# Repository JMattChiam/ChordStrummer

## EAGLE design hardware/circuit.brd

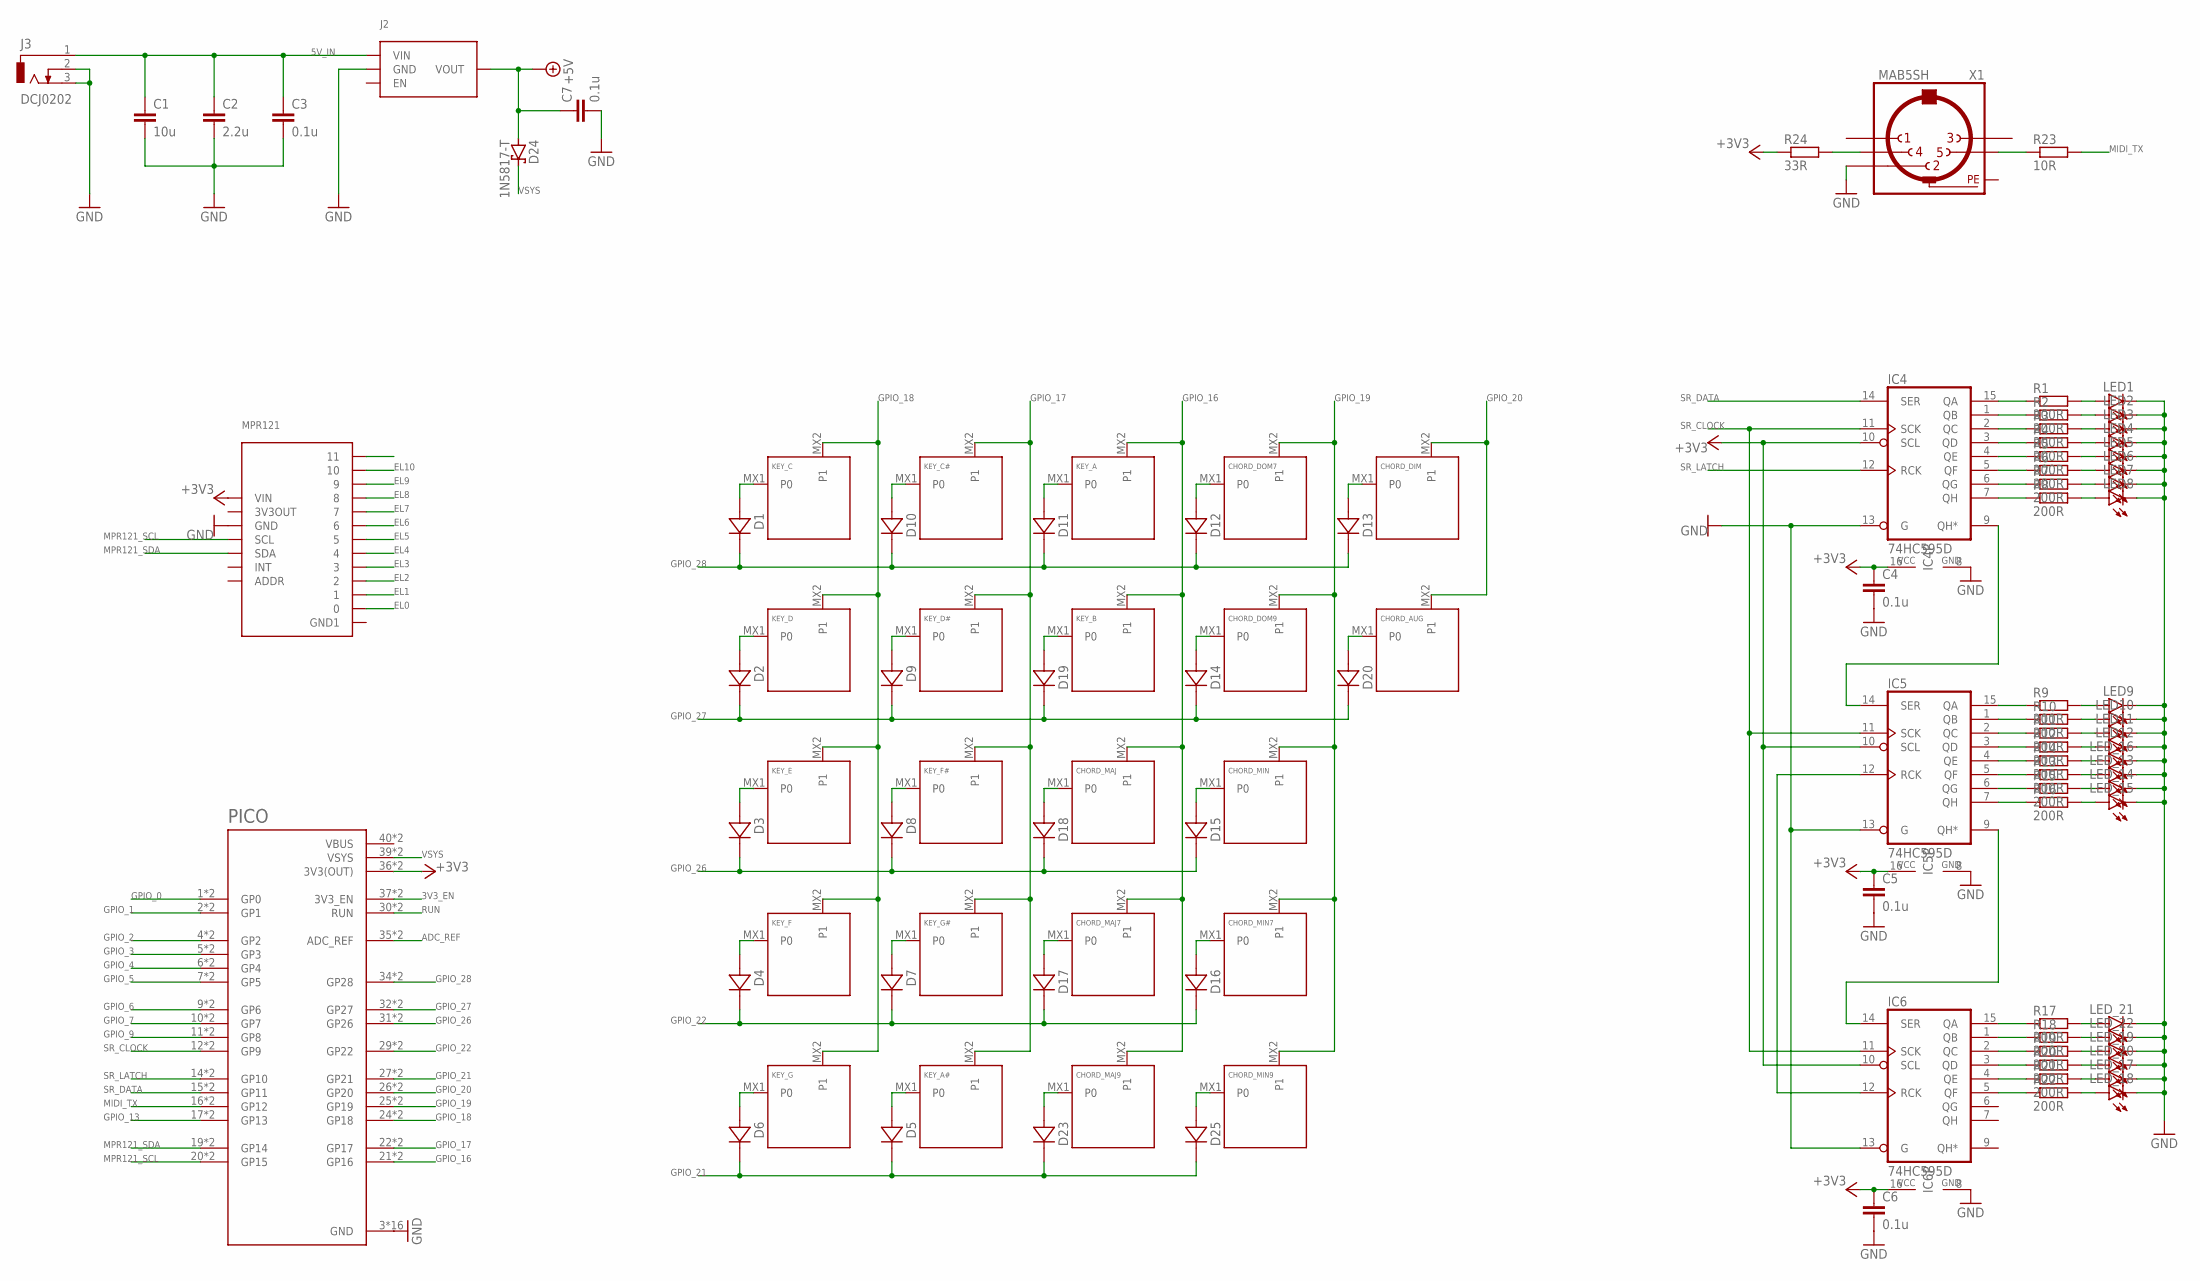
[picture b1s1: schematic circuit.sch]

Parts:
C1: 10u; C5B2.5
C2: 2.2u; C5B2.5
C3, C4, C5, C6, C7: 0.1u; C0805
CHORD_AUG: KEYSWITCH-PLAIN-MX-1U; MX-1U
CHORD_DIM: KEYSWITCH-PLAIN-MX-1U; MX-1U
CHORD_DOM7, CHORD_DOM9: KEYSWITCH-PLAIN-MX-1U; MX-1U
CHORD_MAJ, CHORD_MAJ7, CHORD_MAJ9: KEYSWITCH-PLAIN-MX-1U; MX-1U
CHORD_MIN, CHORD_MIN7, CHORD_MIN9: KEYSWITCH-PLAIN-MX-1U; MX-1U
D1, D2, D3, D4, D5, D6, D7, D8, D9, D10, D11, D12, D13, D14, D15, D16, D17, D18, D19, D20, D23, D25: DIODE-SOD-323; SOD-323
D24: 1N5817-T; DO41-7.6
IC4, IC5, IC6: 74HC595D; SO16
J2: DCDC_MINI_CONVERTER
J3: DCJ0202
KEY_A: KEYSWITCH-PLAIN-MX-1U; MX-1U
KEY_A#: KEYSWITCH-PLAIN-MX-1U; MX-1U
KEY_B: KEYSWITCH-PLAIN-MX-1U; MX-1U
KEY_C: KEYSWITCH-PLAIN-MX-1U; MX-1U
KEY_C#: KEYSWITCH-PLAIN-MX-1U; MX-1U
KEY_D: KEYSWITCH-PLAIN-MX-1U; MX-1U
KEY_D#: KEYSWITCH-PLAIN-MX-1U; MX-1U
KEY_E: KEYSWITCH-PLAIN-MX-1U; MX-1U
KEY_F: KEYSWITCH-PLAIN-MX-1U; MX-1U
KEY_F#: KEYSWITCH-PLAIN-MX-1U; MX-1U
KEY_G: KEYSWITCH-PLAIN-MX-1U; MX-1U
KEY_G#: KEYSWITCH-PLAIN-MX-1U; MX-1U
LED1, LED2, LED3, LED4, LED5, LED6, LED7, LED8, LED9, LED10, LED11, LED12: LEDCHIPLED_0805; CHIPLED_0805
LED_13, LED_14, LED_15, LED_16, LED_17, LED_18, LED_19, LED_20, LED_21, LED_22: LEDCHIPLED_0805; CHIPLED_0805
MPR121: MPR121_ADAFRUIT; ADAFRUIT_MPR121
PICO: RASPBERRY_PICO-NO_DEBUG; PICO-PKG-NO_DEBUG
R1, R2, R3, R4, R5, R6, R7, R8, R9, R10, R11, R12, R13, R14, R15, R16, R17, R18, R19, R20, R21, R22: 200R; R0805
R23: 10R; R0805
R24: 33R; R0805
X1: MAB5SH

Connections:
3V3_EN: PICO.37 (3V3_EN), PICO.P$37 (3V3_EN)
5V_IN: C1.1, C2.1, C3.1, J2.VIN, J3.1
+3V3: C4.1, C5.1, C6.1, IC4.10 (SCL), IC4.16 (VCC), IC5.10 (SCL), IC5.16 (VCC), IC6.10 (SCL), IC6.16 (VCC), MPR121.VCC (VIN), PICO.36 (3V3(OUT)), PICO.P$36 (3V3(OUT)), R24.1
+5V: C7.1, D24.A, J2.VOUT
ADC_REF: PICO.35 (ADC_REF), PICO.P$35 (ADC_REF)
EL0: MPR121.0
EL1: MPR121.1
EL2: MPR121.2
EL3: MPR121.3
EL4: MPR121.4
EL5: MPR121.5
EL6: MPR121.6
EL7: MPR121.7
EL8: MPR121.8
EL9: MPR121.9
EL10: MPR121.10
EL11: MPR121.11
GND: C1.2, C2.2, C3.2, C4.2, C5.2, C6.2, C7.2, IC4.8 (GND), IC4.13 (G), IC5.8 (GND), IC5.13 (G), IC6.8 (GND), IC6.13 (G), J2.GND, J3.2, J3.3, LED1.C, LED2.C, LED3.C, LED4.C, LED5.C, LED6.C, LED7.C, LED8.C, LED9.C, LED10.C, LED11.C, LED12.C, LED_13.C, LED_14.C, LED_15.C, LED_16.C, LED_17.C, LED_18.C, LED_19.C, LED_20.C, LED_21.C, LED_22.C, MPR121.GND, PICO.3 (GND), PICO.8 (GND), PICO.13 (GND), PICO.18 (GND), PICO.23 (GND), PICO.28 (GND), PICO.33 (GND), PICO.38 (GND), PICO.P$3 (GND), PICO.P$8 (GND), PICO.P$13 (GND), PICO.P$18 (GND), PICO.P$23 (GND), PICO.P$28 (GND), PICO.P$33 (GND), PICO.P$38 (GND), X1.2
GPIO_0: PICO.1 (GP0), PICO.P$1 (GP0)
GPIO_1: PICO.2 (GP1), PICO.P$2 (GP1)
GPIO_2: PICO.4 (GP2), PICO.P$4 (GP2)
GPIO_3: PICO.5 (GP3), PICO.P$5 (GP3)
GPIO_4: PICO.6 (GP4), PICO.P$6 (GP4)
GPIO_5: PICO.7 (GP5), PICO.P$7 (GP5)
GPIO_6: PICO.9 (GP6), PICO.P$9 (GP6)
GPIO_7: PICO.10 (GP7), PICO.P$10 (GP7)
GPIO_9: PICO.11 (GP8), PICO.P$11 (GP8)
GPIO_13: PICO.17 (GP13), PICO.P$17 (GP13)
GPIO_16: CHORD_MAJ.MX2 (P1), CHORD_MAJ7.MX2 (P1), CHORD_MAJ9.MX2 (P1), KEY_A.MX2 (P1), KEY_B.MX2 (P1), PICO.21 (GP16), PICO.P$21 (GP16)
GPIO_17: KEY_A#.MX2 (P1), KEY_C#.MX2 (P1), KEY_D#.MX2 (P1), KEY_F#.MX2 (P1), KEY_G#.MX2 (P1), PICO.22 (GP17), PICO.P$22 (GP17)
GPIO_18: KEY_C.MX2 (P1), KEY_D.MX2 (P1), KEY_E.MX2 (P1), KEY_F.MX2 (P1), KEY_G.MX2 (P1), PICO.24 (GP18), PICO.P$24 (GP18)
GPIO_19: CHORD_DOM7.MX2 (P1), CHORD_DOM9.MX2 (P1), CHORD_MIN.MX2 (P1), CHORD_MIN7.MX2 (P1), CHORD_MIN9.MX2 (P1), PICO.25 (GP19), PICO.P$25 (GP19)
GPIO_20: CHORD_AUG.MX2 (P1), CHORD_DIM.MX2 (P1), PICO.26 (GP20), PICO.P$26 (GP20)
GPIO_21: D5.C, D6.C, D23.C, D25.C, PICO.27 (GP21), PICO.P$27 (GP21)
GPIO_22: D4.C, D7.C, D16.C, D17.C, PICO.29 (GP22), PICO.P$29 (GP22)
GPIO_26: D3.C, D8.C, D15.C, D18.C, PICO.31 (GP26), PICO.P$31 (GP26)
GPIO_27: D2.C, D9.C, D14.C, D19.C, D20.C, PICO.32 (GP27), PICO.P$32 (GP27)
GPIO_28: D1.C, D10.C, D11.C, D12.C, D13.C, PICO.34 (GP28), PICO.P$34 (GP28)
MIDI_TX: PICO.16 (GP12), PICO.P$16 (GP12), R23.2
MPR121_SCL: MPR121.SCL, PICO.20 (GP15), PICO.P$20 (GP15)
MPR121_SDA: MPR121.SDA, PICO.19 (GP14), PICO.P$19 (GP14)
unnamed: IC4.9 (QH*), IC5.14 (SER)
unnamed: IC5.9 (QH*), IC6.14 (SER)
unnamed: LED1.A, R1.2
unnamed: LED2.A, R2.2
unnamed: LED3.A, R3.2
unnamed: LED4.A, R4.2
unnamed: LED5.A, R5.2
unnamed: LED6.A, R6.2
unnamed: LED7.A, R7.2
unnamed: LED8.A, R8.2
unnamed: LED9.A, R9.2
unnamed: LED10.A, R10.2
unnamed: LED11.A, R11.2
unnamed: LED12.A, R12.2
unnamed: LED_16.A, R14.2
unnamed: LED_13.A, R13.2
unnamed: LED_15.A, R16.2
unnamed: LED_14.A, R15.2
unnamed: LED_21.A, R17.2
unnamed: LED_22.A, R18.2
unnamed: LED_19.A, R19.2
unnamed: LED_20.A, R20.2
unnamed: LED_17.A, R21.2
unnamed: LED_18.A, R22.2
unnamed: IC4.15 (QA), R1.1
unnamed: IC4.1 (QB), R2.1
unnamed: IC4.2 (QC), R3.1
unnamed: IC4.3 (QD), R4.1
unnamed: IC4.4 (QE), R5.1
unnamed: IC4.5 (QF), R6.1
unnamed: IC4.6 (QG), R7.1
unnamed: IC4.7 (QH), R8.1
unnamed: IC5.15 (QA), R9.1
unnamed: IC5.1 (QB), R10.1
unnamed: IC5.2 (QC), R11.1
unnamed: IC5.3 (QD), R12.1
unnamed: IC5.5 (QF), R13.1
unnamed: IC5.4 (QE), R14.1
unnamed: IC5.6 (QG), R15.1
unnamed: IC5.7 (QH), R16.1
unnamed: IC6.15 (QA), R17.1
unnamed: IC6.1 (QB), R18.1
unnamed: IC6.2 (QC), R19.1
unnamed: IC6.3 (QD), R20.1
unnamed: IC6.4 (QE), R21.1
unnamed: IC6.5 (QF), R22.1
unnamed: R23.1, X1.5
unnamed: R24.2, X1.4
unnamed: CHORD_MAJ9.MX1 (P0), D23.A
unnamed: CHORD_MIN9.MX1 (P0), D25.A
unnamed: D1.A, KEY_C.MX1 (P0)
unnamed: D10.A, KEY_C#.MX1 (P0)
unnamed: D11.A, KEY_A.MX1 (P0)
unnamed: CHORD_DOM7.MX1 (P0), D12.A
unnamed: CHORD_DIM.MX1 (P0), D13.A
unnamed: D2.A, KEY_D.MX1 (P0)
unnamed: D3.A, KEY_E.MX1 (P0)
unnamed: D4.A, KEY_F.MX1 (P0)
unnamed: D6.A, KEY_G.MX1 (P0)
unnamed: D5.A, KEY_A#.MX1 (P0)
unnamed: D7.A, KEY_G#.MX1 (P0)
unnamed: D8.A, KEY_F#.MX1 (P0)
unnamed: D9.A, KEY_D#.MX1 (P0)
unnamed: D19.A, KEY_B.MX1 (P0)
unnamed: CHORD_MAJ.MX1 (P0), D18.A
unnamed: CHORD_MAJ7.MX1 (P0), D17.A
unnamed: CHORD_MIN7.MX1 (P0), D16.A
unnamed: CHORD_MIN.MX1 (P0), D15.A
unnamed: CHORD_DOM9.MX1 (P0), D14.A
unnamed: CHORD_AUG.MX1 (P0), D20.A
PE: X1.PE, X1.PE@ (PE)
RUN: PICO.30 (RUN), PICO.P$30 (RUN)
SR_CLOCK: IC4.11 (SCK), IC5.11 (SCK), IC6.11 (SCK), PICO.12 (GP9), PICO.P$12 (GP9)
SR_DATA: IC4.14 (SER), PICO.15 (GP11), PICO.P$15 (GP11)
SR_LATCH: IC4.12 (RCK), IC5.12 (RCK), IC6.12 (RCK), PICO.14 (GP10), PICO.P$14 (GP10)
VBUS: PICO.40 (VBUS), PICO.P$40 (VBUS)
VSYS: D24.C, PICO.39 (VSYS), PICO.P$39 (VSYS)

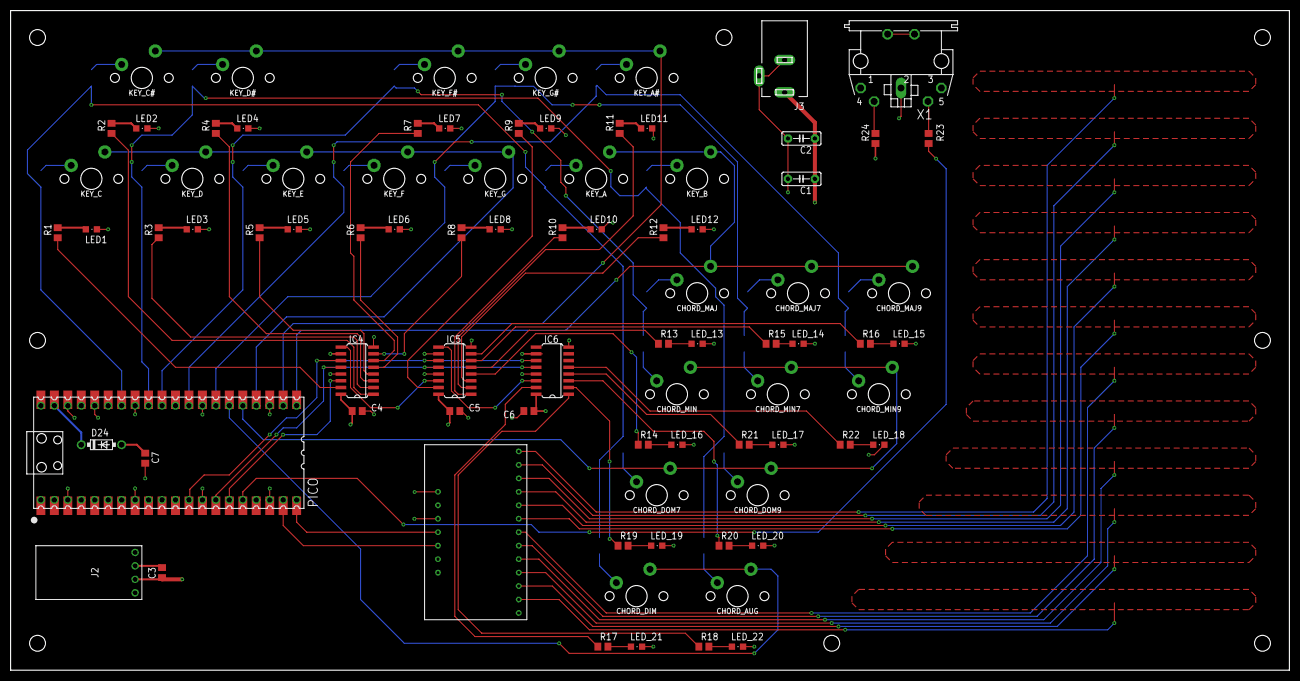
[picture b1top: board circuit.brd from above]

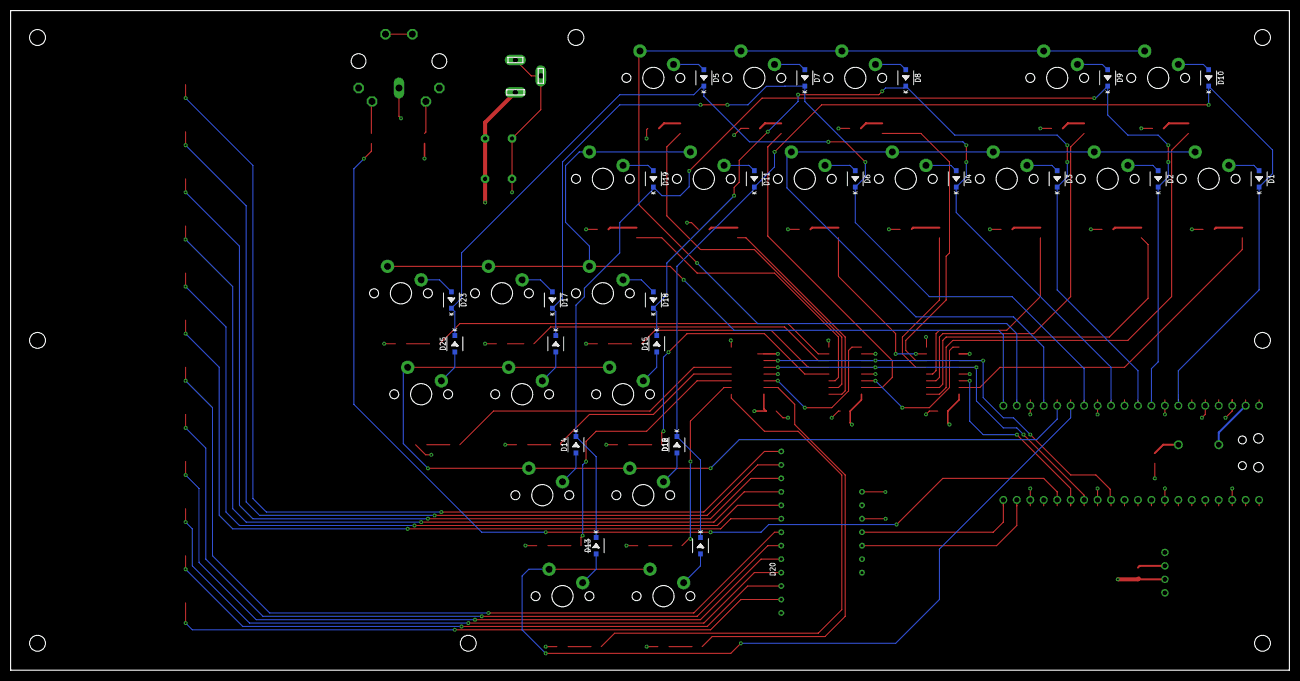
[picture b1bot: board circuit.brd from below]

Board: 4 copper layers, 241.3 x 124.5 mm, 106 parts (22 on the bottom side), 106 nets.

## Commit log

2023-06-08 add build
2023-06-09 Update chord voicings
2023-06-12 Add EAGLE files
2023-06-14 Add chord.h and change to matrix scanning algorithm for keyswitches
2023-06-14 Add LED hex mappings
2023-06-15 Add code for using 74hc595 shift register
    Refactor rootNote variable use the Notes enum
    This is to maintain consistency that the rootNote is always referred to
    by the enum (0 to 12). Conversion to MIDI number is done by the
    getMIDINote() function
2023-06-23 Fix bugs
    Board has been soldered. Scanning and LEDs all working now.
2023-07-03 Add MIDI uart
2023-07-03 Debug
2023-09-24 Add 3D model for case
